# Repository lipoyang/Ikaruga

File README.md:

# 斑鳩ボード
## 概要
斑鳩ボードは、Nordic nRF52832搭載のBLEマイコンボードです。 

## 仕様
* BLEマイコンnRF52832搭載 (Bluetooth 4.2 / ARM Cortex-M4F)
* 技適取得済みnRF52832モジュール Liard BL652を使用
* Arduino Pro Miniピン互換 (GR-KURUMIやGR-CITRUSとも共通)
* nRF52-DKの開発環境（mbedやnRF5 SDK）で開発
* nRF52-DK や BLE Nano V2のDAPLinkボードをアダプタとして使う
* 300mAのLDO、3色のLED、32.768kHzサブクロック、リセットスイッチを搭載

## ピン配置

## 開発環境 (mbed)
* mbed Compiperのプラットフォーム選択でNordic nRF52-DKを選びます。
* BLE Nano V2のDAPLinkボードを使う場合、斑鳩を下図ように結線します。
* あとは、ふつうにmbedの要領で開発します。

## nRF52-DKをアダプタに使う場合
最低限、結線が必要なのは以下の4本です。

* GND DETECT　→　ターゲットのGNDに接続
* VTG　→　ターゲットの電源電圧(VDD_nRF)に接続
* SWD CLK　→　ターゲットのSWDCLKに接続
* SWD IO　→　ターゲットのSWDIOに接続

加えて、nRF52-DKボードから斑鳩ボードに給電する場合には以下の2本を結線します。

* GND　→　ターゲットのGNDに接続
* VDD　→　ターゲットの電源電圧(VDD_nRF)に接続

## Ｌチカ (mbed)
```C
#include "mbed.h"

DigitalOut myled1(LED1); // Blue
DigitalOut myled2(LED2); // Yellow
DigitalOut myled3(LED3); // Red

int main() {
    while(1) {
        myled1 = 1;
        wait(0.5);
        myled2 = 1;
        wait(0.5);
        myled3 = 1;
        wait(0.5);
        myled1 = 0;
        wait(0.5);
        myled2 = 0;
        wait(0.5);
        myled3 = 0;
        wait(0.5);
    }
}
```

## ファイル一覧
* hard/Ikaruga/
	* Ikaruga.sch/brd: 回路/基板設計データ(Eagle形式)
	* Ikaruta.pdf: 回路図(PDF)
	* Ikaruga_BOM.xlsx: BOMリスト(Excel形式)
	* Ikaruga.GBL/GBO/GBP/GBS/GML/GTL/GTO/GTP/GTS/TXT: ガーバデータ
* LICENSE: Apache Licence 2.0です。
	* ただし、回路/基板設計は、Creative Commons Attribution Share-Alike 3.0です。
* README.md これ

## 注意
「斑鳩」は「いかるが」と読みます。  
聖徳太子と法隆寺で有名です。難読地名とか言わないでください。

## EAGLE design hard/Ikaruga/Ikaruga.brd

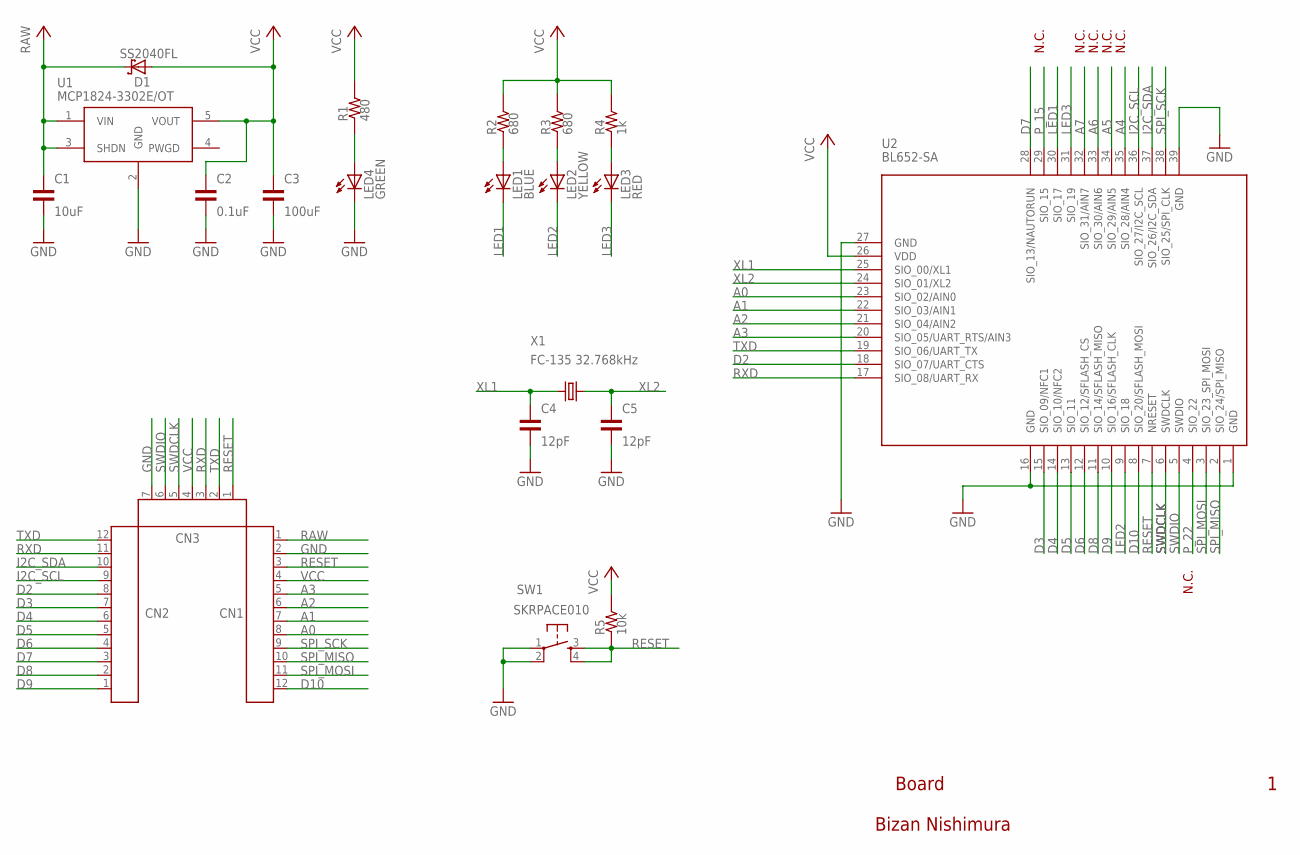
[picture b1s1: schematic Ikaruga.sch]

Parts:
C1: 10uF; CP3216
C2: 0.1uF; CP1608
C3: 100uF; CP3216
C4, C5: 12pF; CP1608
CN1, CN2: PINHD-1X12-NO-LINE; 1X12-NO-LINE
CN3: PINHD-1X7-NO-LINE; 1X07-NO-LINE
D1: SS2040FL; SOD123
LED1: BLUE; LED1608
LED2: YELLOW; LED1608
LED3: RED; LED1608
LED4: GREEN; LED1608
R1: 480; CP1608
R2, R3: 680; CP1608
R4: 1k; CP1608
R5: 10k; CP1608
SW1: SKRPACE010
U1: MCP1824-3302E/OT; SOT-23-5
U2: BL652-SA
X1: FC-135 32.768kHz; FC-135

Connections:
A0: CN1.8, U2.23 (SIO_02/AIN0)
A1: CN1.7, U2.22 (SIO_03/AIN1)
A2: CN1.6, U2.21 (SIO_04/AIN2)
A3: CN1.5, U2.20 (SIO_05/UART_RTS/AIN3)
A4: U2.35 (SIO_28/AIN4)
A5: U2.34 (SIO_29/AIN5)
A6: U2.33 (SIO_30/AIN6)
A7: U2.32 (SIO_31/AIN7)
D2: CN2.8, U2.18 (SIO_07/UART_CTS)
D3: CN2.7, U2.15 (SIO_09/NFC1)
D4: CN2.6, U2.14 (SIO_10/NFC2)
D5: CN2.5, U2.13 (SIO_11)
D6: CN2.4, U2.12 (SIO_12/SFLASH_CS)
D7: CN2.3, U2.28 (SIO_13/NAUTORUN)
D8: CN2.2, U2.11 (SIO_14/SFLASH_MISO)
D9: CN2.1, U2.10 (SIO_16/SFLASH_CLK)
D10: CN1.12, U2.8 (SIO_20/SFLASH_MOSI)
GND: C1.SMD2 (PIN2), C2.SMD2 (PIN2), C3.SMD2 (PIN2), C4.SMD2 (PIN2), C5.SMD2 (PIN2), CN1.2, CN3.7, LED4.C, SW1.1, SW1.2, U1.2 (GND), U2.1 (GND), U2.16 (GND), U2.27 (GND), U2.39 (GND)
I2C_SCL: CN2.9, U2.36 (SIO_27/I2C_SCL)
I2C_SDA: CN2.10, U2.37 (SIO_26/I2C_SDA)
LED1: LED1.C, U2.30 (SIO_17)
LED2: LED2.C, U2.9 (SIO_18)
LED3: LED3.C, U2.31 (SIO_19)
unnamed: LED4.A, R1.SMD1 (PIN1)
unnamed: LED1.A, R2.SMD1 (PIN1)
unnamed: LED2.A, R3.SMD1 (PIN1)
unnamed: LED3.A, R4.SMD1 (PIN1)
P_15: U2.29 (SIO_15)
P_22: U2.4 (SIO_22)
RAW: C1.SMD1 (PIN1), CN1.1, D1.C, U1.1 (VIN), U1.3 (SHDN)
RESET: CN1.3, CN3.1, R5.SMD1 (PIN1), SW1.3, SW1.4, U2.7 (NRESET)
RXD: CN2.11, CN3.3, U2.17 (SIO_08/UART_RX)
SPI_MISO: CN1.10, U2.2 (SIO_24/SPI_MISO)
SPI_MOSI: CN1.11, U2.3 (SIO_23_SPI_MOSI)
SPI_SCK: CN1.9, U2.38 (SIO_25/SPI_CLK)
SWDCLK: CN3.5, U2.6 (SWDCLK)
SWDIO: CN3.6, U2.5 (SWDIO)
TXD: CN2.12, CN3.2, U2.19 (SIO_06/UART_TX)
VCC: C2.SMD1 (PIN1), C3.SMD1 (PIN1), CN1.4, CN3.4, D1.A, R1.SMD2 (PIN2), R2.SMD2 (PIN2), R3.SMD2 (PIN2), R4.SMD2 (PIN2), R5.SMD2 (PIN2), U1.5 (VOUT), U2.26 (VDD)
XL1: C4.SMD1 (PIN1), U2.25 (SIO_00/XL1), X1.1
XL2: C5.SMD1 (PIN1), U2.24 (SIO_01/XL2), X1.2

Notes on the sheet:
Bizan Nishimura
Board
N.C.

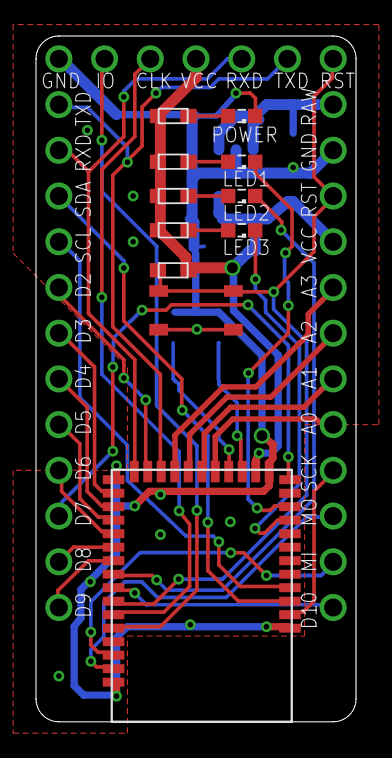
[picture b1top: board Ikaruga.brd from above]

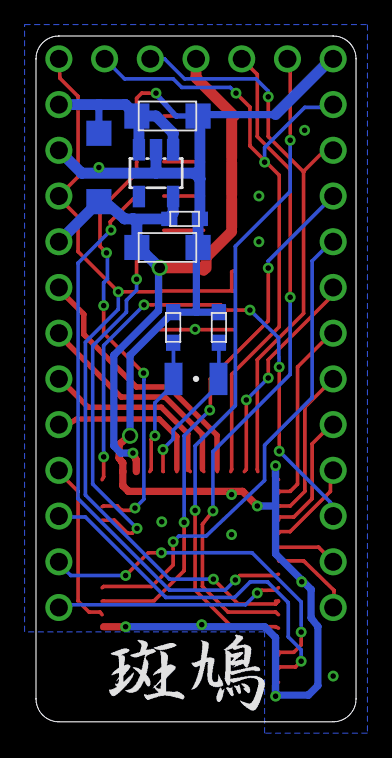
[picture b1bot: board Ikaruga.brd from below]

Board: 2 copper layers, 17.8 x 38.1 mm, 23 parts (8 on the bottom side), 35 nets.

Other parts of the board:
U$1: IKARUGA_B

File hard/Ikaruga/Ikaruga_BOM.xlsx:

Ikaruga Board BOM
No | Reference | Part Number | Vender | Description | DNP | Qty | Unit Price | Price | Lot Size | Supplier | Supplier Code
1 | C1 | 10u(3216) | (generic) | 3216型ガタ |  | 1 | 25 | 25 | 10 | 秋月アキヅキ | P-06462
2 | C2 | 0.1u(1608) | (generic) | 1608型ガタ |  | 1 | 0.32500000000000001 | 0.32500000000000001 | 4000 | 秋月アキヅキ | P-01299
3 | C3 | 47u(3216) | (generic) | 3216型ガタ |  | 1 | 30 | 30 | 10 | 秋月アキヅキ | P-06040
4 | C4,5 | 12pF(1608) | (generic) | 1608型ガタ |  | 2 | 1.8 | 3.6 | 100 | 秋月アキヅキ | P-05521
5 | CN1,2 | - | (generic) | 2.54mmピッチ 12ピン×1列 ピンヘッダレツ | DNP | 0 | 0 | 0 | 1 | 共立キョウリツ | -
6 | CN3 | - | (generic) | 2.54mmピッチ 7ピン×1列 ピンヘッダレツ | DNP | 0 | 0 | 0 | 2 | 共立キョウリツ | -
7 | D1 | SS2040FL | PANJIT | ショットキーバリアダイオード 40V2A |  | 1 | 15 | 15 | 20 | 秋月アキヅキ | I-02073
8 | LED1 | OSBL1608 | OptoSupply | 1608型 BLUEガタ |  | 1 | 10 | 10 | 20 | 秋月アキヅキ | I-03982
9 | LED2 | OSYL1608 | OptoSupply | 1608型 YELLOWガタ |  | 1 | 10 | 10 | 20 | 秋月アキヅキ | I-03984
10 | LED3 | OSHR1608 | OptoSupply | 1608型 REDガタ |  | 1 | 10 | 10 | 20 | 秋月アキヅキ | I-03978
11 | LED4 | OSYG1608 | OptoSupply | 1608型 GREENガタ |  | 1 | 10 | 10 | 20 | 秋月アキヅキ | I-03980
12 | R1 | 470(1608) | (generic) | 1608型 |  | 1 | 0.2 | 0.2 | 2500 | 秋月アキヅキ | R-06471
13 | R2,3 | 680(1608) | (generic) | 1608型 |  | 2 | 2.48 | 4.96 | 100 | RS | 391-5258
14 | R4 | 1k(1608) | (generic) | 1608型 |  | 1 | 0.2 | 0.2 | 2500 | 秋月アキヅキ | R-06102
15 | R5 | 10k(1608) | (generic) | 1608型、±0.1% |  | 1 | 0.2 | 0.2 | 2500 | 秋月アキヅキ | R-06103
16 | SW1 | SKRPACE010 | ALPS | 表面実装タクトスイッチヒョウメンジッソウ |  | 1 | 20 | 20 | 5 | 秋月アキヅキ | P-06185
17 | U1 | MCP1824-3302E/OT | Microchip | LDO 3.3V 300mA SOT-23 5ピン |  | 1 | 57.2 | 57.2 | 1 | RS | 669-5011
18 | U2 | BL652-SA | Laird | nRF52832搭載 BLEマイコンモジュールトウサイ |  | 1 | 905 | 905 | 1 | Digi-Key | BL652-SA-01-CT-ND
19 | X1 | FC-135 32.768kHz | Epson | 水晶発振子 32.768kHzスイショウハッシンコ |  | 1 | 40 | 40 | 5 | 秋月アキヅキ | P-07195
20 | - | - | Elecrow | 基板キバン |  | 1 | 262.39999999999998 | 262.39999999999998 | 10 | Elecrow | -
 |  |  |  |  |  |  | Total | 1404.085

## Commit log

2019-10-11 add files
2019-10-11 add README
2019-10-11 add .gitattributes

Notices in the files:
parts and their libraries:
lipoyang_frame: Released under the Creative Commons
Attribution Share-Alike 3.0 License
http://creativecommons.org/licenses/by-sa/3.0
